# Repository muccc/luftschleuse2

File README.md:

luftschleuse2
=============

Second incarnation of our access system.

See http://wiki.muc.ccc.de/luftschleuse2:overview for more details about this system.

See http://wiki.muc.ccc.de/luftschleuse2:simulation if you want to simulate a luftschleuse2 system.

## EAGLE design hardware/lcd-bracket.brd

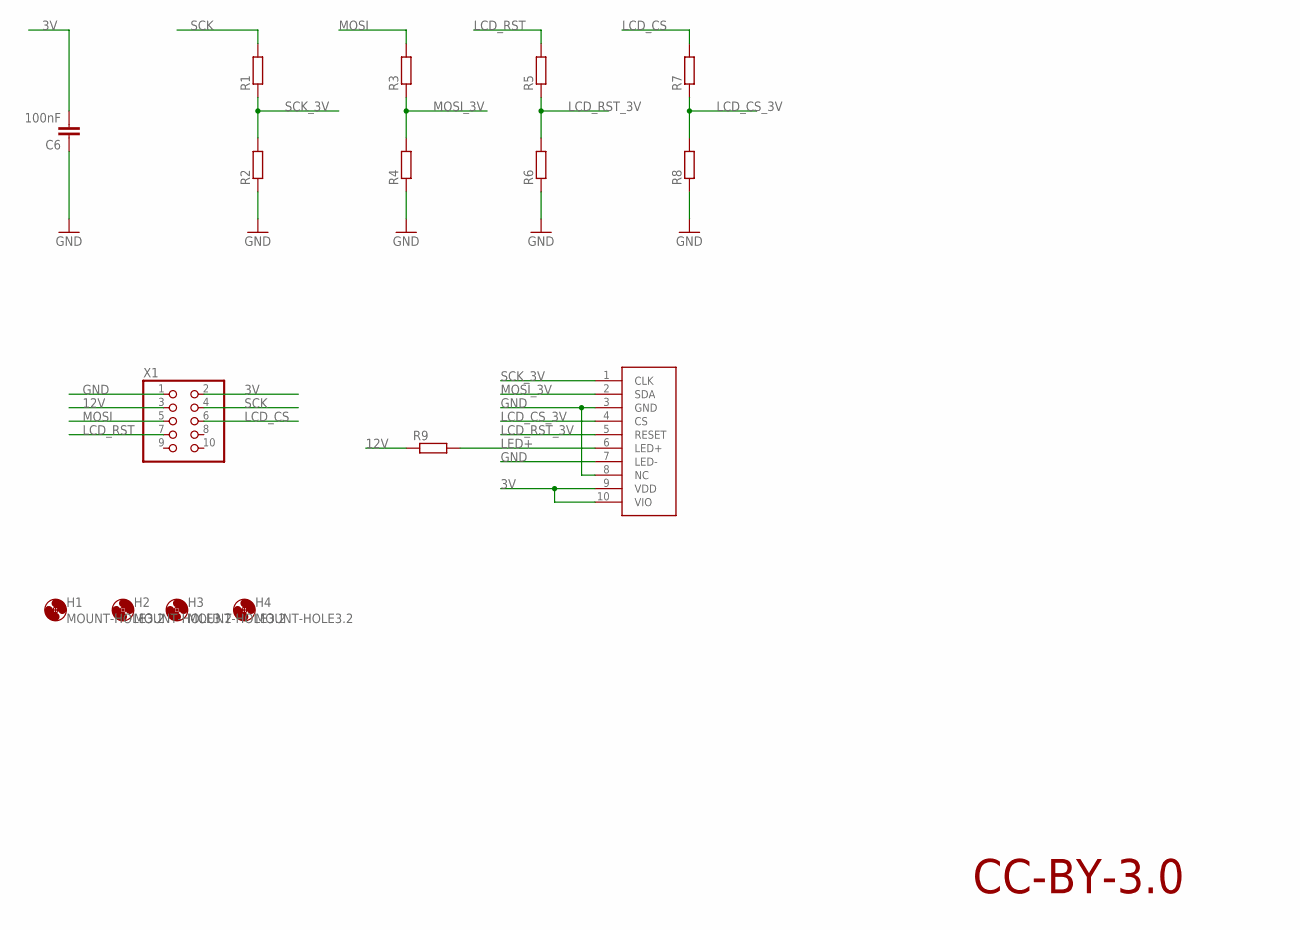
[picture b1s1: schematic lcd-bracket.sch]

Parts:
C6: 100nF; C0603K
H1, H2, H3, H4: MOUNT-HOLE3.2; 3,2
R1, R2, R3, R4, R5, R6, R7, R8: R-EU_R0603; R0603
R9: R-EU_R1206; R1206
X1: PINHD-2X5; 2X05
X2: NOKIA; DF23

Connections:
3V: C6.2, X1.2, X2.9 (VDD), X2.10 (VIO)
12V: R9.1, X1.3
GND: C6.1, R2.1, R4.1, R6.1, R8.1, X1.1, X2.3 (GND), X2.7 (LED-), X2.8 (NC)
LCD_CS: R7.2, X1.6
LCD_CS_3V: R7.1, R8.2, X2.4 (CS)
LCD_RST: R5.2, X1.7
LCD_RST_3V: R5.1, R6.2, X2.5 (RESET)
LED+: R9.2, X2.6 (LED+)
MOSI: R3.2, X1.5
MOSI_3V: R3.1, R4.2, X2.2 (SDA)
SCK: R1.2, X1.4
SCK_3V: R1.1, R2.2, X2.1 (CLK)

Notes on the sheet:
CC-BY-3.0

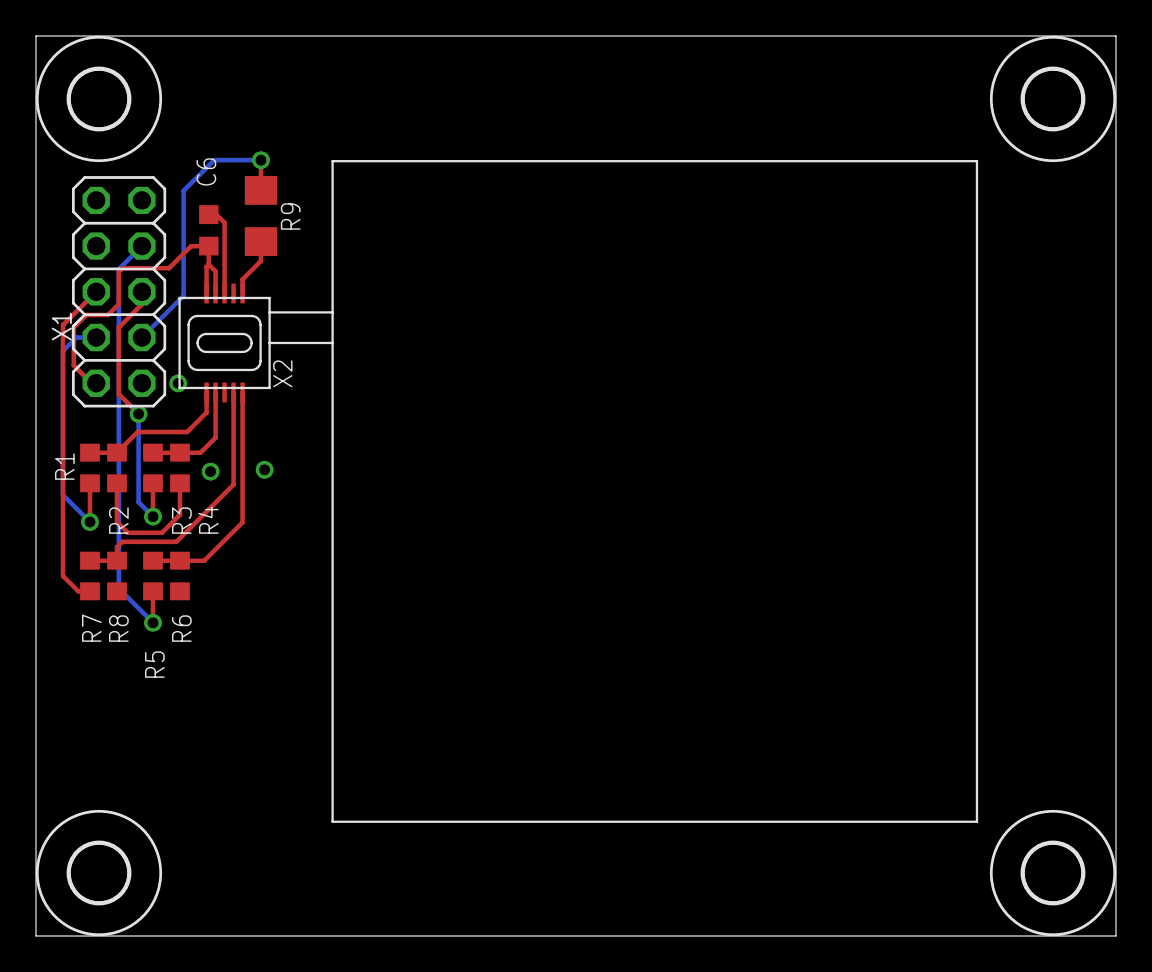
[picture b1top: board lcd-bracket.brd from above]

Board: 2 copper layers, 60.0 x 50.0 mm, 16 parts (0 on the bottom side), 12 nets.

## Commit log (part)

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2012-12-09 added breakout for the lcd of the master controller
2012-12-12 directory structure
2012-12-12 parts of the avr cryptolib from das-labor.org
2012-12-12 serial communication base files for lockd
2012-12-12 stubs for mastercontroller and lockcontroller
2012-12-12 removed unneeded binaries
2012-12-12 moved crypto-lib
2012-12-13 moved crypto lib into a real library
2012-12-13 example code to use the aes functions
2012-12-13 serial interface for mastercontroller
2012-12-13 stub for lockd
2012-12-13 added aes test
2012-12-13 encrypting structs
2012-12-16 Added Layout Files
2013-01-06 first bytes flowing down the pipe
2013-01-12 added serial forwarding
2013-01-12 added simple command interface
2013-01-12 more commands
2013-01-12 refactor of packet magic check
2013-01-12 encrypt decrypt packets on the bus
2013-01-13 added set doorstate command
2013-01-13 refactored door command structure
2013-01-14 more door logic
2013-01-27 cosmetics
2013-02-02 adc, support for new test lock, acks with result
2013-02-02 lockd: more abstraction
2013-02-02 bug hunting
2013-02-02 cmd acceptance is displayed
2013-02-02 simple udp command interface
2013-02-03 first approach on error detection
2013-03-01 testcode for second door type
2013-03-09 first version that locked the door over a distance
2013-03-24 lc: blink support for leds
2013-03-24 lc: debonce a single buttons
2013-03-24 lc: updated main loop
2013-03-24 door-2: break motor when reaching the desired state, start moving as soon as the door is closed
2013-03-24 lc: use button to toggle the state
2013-03-24 lockd: added python only aes lib
2013-03-24 lockd: removed requirements for crc16 and pycrypto
2013-03-24 renamed files
2013-03-24 new state system
2013-03-24 lockd: bug fixes and button to open and close per door
2013-03-24 lockcontroller: only try to open/close if the handle is not pressed
2013-03-24 lockcontroller: led shows state of the lock
2013-03-25 moved to lached buttons to prevent issues when the lockcontroller resets
2013-03-26 lockd: initiate pressed_buttons, faster polling
2013-03-26 lockd: make it killable via Ctrl+C
2013-03-27 added some logging
2013-03-27 lockd: first try for logging
2013-03-27 bugfix
2013-03-27 lockd: show desired state
2013-03-28 lockd: bugfix
2013-03-28 lockd: put elapsed time into exception when the port seems broken
2013-03-28 lockd: more relaxed handling of interface timeouts
2013-03-31 lockd: disabled restarting of lockd when the serial port seems broken
2013-04-01 button and irc integration
2013-04-01 button and led integration
2013-04-01 lockcontroller: new lock logic
2013-05-01 Only unlock specific doors via ssh
2013-05-01 git key mangement hook
2013-05-01 file to switch on the serial port on the carambola
2013-05-01 more carambola config files
2013-05-01 updated gitignore
2013-05-04 first lines for the doorlogic
2013-05-04 doorlogic for new user interface
2013-05-04 lockd: serialinterface: open logger before logging error
2013-05-04 lockd: doorlogic: syntax errors
2013-05-05 lockd: use DoorLogic in the main loop
2013-05-05 lockd: udp, master: use new doorlogic
2013-05-05 lockd: internal command: 'down'
2013-05-05 lockd: initial_unlock in config file
2013-05-05 lockd: new config section for master controller buttons, bug fixes
2013-05-06 lockd: made polling of the door independent of the used timeout of the serial line
2013-05-09 lockd: updated door.py for new doorlogic
2013-05-09 lockd: announce the full state
2013-05-09 lockd: typo in config
2013-05-12 new vector names inside the uart lib
2013-05-12 fixed new vector names inside the uart lib
2013-05-12 lockcontroller: first bell code implementation
2013-06-06 added notes to the door configuration
2013-06-06 firmwre for new mode control
2013-06-08 small clean up
2013-06-08 more cleanup
2013-06-08 added interface controller for the leds
2013-06-08 bug fixes
2013-06-08 added bellcode support to lockd
2013-06-09 bugfix for bell code detection
2013-06-09 made the public button a toggle switch
2013-06-10 added reed contact to determine door state
2013-06-10 Slowed down programmer
2013-06-12 design files for the laser cut front panel
2013-06-20 switched to latest uart lib
2013-06-20 removed bad port init from lockcntroller
2013-06-20 separated the config for the two doors
2013-06-20 added script to mount our device via sshfs
2013-06-20 mount-schleuse: added missing mkdir
2013-06-21 fixed build system and made reed cotacts work
2013-06-22 removed dead BUS_AUTO_QUERY code
2013-06-23 disabled encryption for the master controller. enabled seq number checking for the doors.
2013-06-23 moved config parsing of door sections to door class
2013-06-23 fixed bug in incrementing rx sequence number inside lockconrollers
2013-06-23 added rx sequence storage inside the lockd config
2013-06-23 small bugfixes
2013-06-23 added script to generate a key
2013-06-28 added rate limit to the udp command receiver
2013-06-28 progress on the lcd hal
2013-06-29 working code for nokia 1600 displays
2013-06-30 mastercontroller: initial nokia 1600 support
2013-06-30 removed old 1600 boarder
2013-06-30 added python class to speak to a display, connected to the mastercontroller
2013-06-30 fixed off by one in the display size
2013-07-01 based display driver on PIL
2013-07-01 Removed possiby uneeded sleep in the serial communication
2013-07-01 updated the simple display test
2013-07-01 updated display test
2013-07-01 added file to test the font rendering performance of pil
2013-07-01 added display support to lockd
2013-07-01 added simulated display
2013-07-01 added config to test lockd locally
2013-07-01 added display simualtion over network
2013-07-01 display doing stuff :)
2013-07-01 missing file for display network emulation
2013-07-01 lcd fixes
2013-07-01 do not use image.tobytes()
2013-07-01 added a bit more logging
2013-07-01 display: only send 16 bytes at a time...
2013-07-01 door: only update other system parts if something changes
2013-07-01 more debug output
2013-07-01 enforce at least 4 s between each display update
2013-07-02 fixed off by one error in magic value comparison
2013-07-02 small performance improvement in the serial process
2013-07-02 eagle gitignore
2013-07-10 first lines of documentation ;)
2013-07-11 updated protocol description
2013-07-14 removed dead code
2013-07-14 tests for the master controller
2013-07-14 added first unittest
2013-07-14 more tests for the master controller
2013-07-14 added first door tests
2013-07-15 added encrypted message decoding to Packet
2013-07-15 removed aes from Door
2013-07-15 more tests for Door
2013-07-20 Update LOCK-BUS-PROTOCOL
2013-07-20 update to the lock bus protocol
2013-07-20 added tests for door.py, modified handling of sequence numbers
2013-07-20 disabled verbose debug output in the door test
2013-07-20 doorlogic test stub
2013-07-23 more doorlogic tests
2013-07-25 license information for lockd
2013-07-26 fixes #22: write rx sequence numbers to a separate file
2013-07-27 put lockd code into a class
2013-07-27 door.py detects failed lockcontrollers
2013-07-27 added error states to the display
2013-07-27 made update rate for the display configurable
2013-07-28 log all changes of a door state
2013-07-28 added uart-network-bridge.c to receive data from the master
2013-07-28 added native delay operations
2013-07-28 added skeleton for master controller simulation
2013-07-28 reduced cpu load
2013-07-28 prepared the master controller for simulation
2013-07-28 simulated mastercontroller and master talk to each other
2013-07-28 added simulated lockcontrollers
2013-07-28 added simulated lockcontrollers: missed some files
2013-07-28 added config file for lockd
2013-07-29 full master simulation with cli
2013-07-29 working cli for the lockcontroller
2013-07-30 added display mock to the simulated master controller
2013-07-30 lockd: use the mock lcd when simulating the system
2013-07-31 moved to sdl-config for SDL configuration
2013-07-31 credits for SDL
2013-07-31 restrict unicats UDP to localhost
2013-07-31 updated license stuff
2013-08-01 added english overview graph
2013-08-01 added rpi as target option in the graph
2013-08-01 added master controller simulation picture
2013-08-01 lockd: refresh the master LEDs from time to time
2013-08-01 git: ignore .dep files
2013-08-01 lockcontroller_simulation: start with a closed door
2013-08-01 added links to the wiki
2013-08-01 fixed bug which causes too many eeprom writes
2013-08-01 added leaky bucket counter to prevent the lock controller from getting flodded
2013-08-01 added screenshot of simulated lock controller
2013-08-01 syslog receiver: print timestamps
2013-08-01 lockd: removed unneeded debug messages for the master controller
2013-08-01 harmonized the manual_unlocked and perm_unlocked flags
2013-08-01 added bell simulation to the lock controller simulation
2013-08-01 lockd: fixed broken bell code
2013-08-01 lockd: adden "open" state to the display
2013-08-01 modified door led logic
2013-08-03 lockd: fixed broken min rx seq persistence
2013-08-03 lockd: implemented a priority queue for the serial interface
2013-08-03 fixed bug in the doorlogic when handling buttons
2013-08-03 moved to pycrypto
2013-08-03 removed unused aes.py file
2013-08-03 renamed interfacelogic to userinterfacelogic
2013-08-03 missing file for the lock controller simulation
2013-08-03 small door.py cleanup
2013-08-03 removed sleeps from display.py
2013-09-16 New version for lockcontroller
2013-11-06 Feste Zeiten fuer bell_process entfernt.
    Es werden jetzt die Beeps in kurze und lange gebinnt und dann mit dem Code verglichen.
2013-11-06 Debugging printfs entfernt
2014-06-15 chore(door-2): remove unused pin R1
2014-11-10 feat(lockcontroller): add new door model
2014-11-10 feat(demo-door): Add demo door project
2014-11-10 fix(lockcontroller_V2): Add schematic
2014-11-10 fix(demo-door): Set address of demo door to C
2016-01-26 feat(lockd): Write the system state to a temp file
2016-01-26 feat(lockd): Add unlockfront command
2016-01-26 feat(lockd): Only unlock the front door in public mode
2016-01-26 feat(hostapd): Add hostapd wifi name script
2022-02-25 WIPPERIA
2022-02-25 serialinterface: use bytes for RX
2022-02-25 lockd: parse door address as bytes
2022-02-26 add nix flake for lockd & std python layout
2022-02-26 modify hostapd state change
2022-02-26 lockd: fix serial api
2022-02-26 poetry: Python 3.8 is good enough
2022-02-27 change wlan ssid from update_state function
2022-03-26 lockd: tick can happen if not changed
2022-03-26 serialinterface: handle delays after write
2022-03-26 door: add a 20 ms delay after writing a command
2022-03-26 lockd: use normal strings for commands
2022-03-26 change ssid only on state change
2022-09-08 lockd: disable hostapd integration (external AP used)
2022-09-13 lockd: disable button pannel, toggle state via door lock buttons
2022-09-13 lockd: fix door locking logic in state toggle
2022-09-21 lockd: allow to set state via network
2022-09-21 update deps
2022-09-21 add concierge service to replace pannel & bellcode
2022-10-28 Revert "lockd: fix door locking logic in state toggle"
    This reverts commit fb83d6541531fd22f161826a064a65e83d75d4ca.
2022-10-28 Revert "lockd: disable button pannel, toggle state via door lock buttons"
    This reverts commit ccbbf6a40032579dcaf00971ed17d5e8def945da.
2022-11-05 make nix flake compliant
2023-07-16 flake.lock: Update
    Flake lock file updates:
    • Updated input 'flake-utils':
    'github:numtide/flake-utils/5aed5285a952e0b949eb3ba02c12fa4fcfef535f' (2022-11-02)
    → 'github:numtide/flake-utils/919d646de7be200f3bf08cb76ae1f09402b6f9b4' (2023-07-11)
    • Added input 'flake-utils/systems':
    'github:nix-systems/default/da67096a3b9bf56a91d16901293e51ba5b49a27e' (2023-04-09)
2023-07-16 nix: reformat
2023-07-16 lockd: poetry update
2024-02-05 concierge: remove
2024-02-05 poetry update
2024-05-10 flake.lock: Update
    Flake lock file updates:
    • Updated input 'flake-utils':
    'github:numtide/flake-utils/919d646de7be200f3bf08cb76ae1f09402b6f9b4' (2023-07-11)
    → 'github:numtide/flake-utils/b1d9ab70662946ef0850d488da1c9019f3a9752a' (2024-03-11)
    • Updated input 'nixpkgs':
    'github:NixOS/nixpkgs/8acef304efe70152463a6399f73e636bcc363813' (2023-07-15)
2024-10-03 lockd/annouce: bind to ipv6 socket
